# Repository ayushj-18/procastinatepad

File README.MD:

# procastinatepad
I like to procastinate alot so I made a hackpad to procastinate other stuff with it
## A hackpad with a 2x4 matrix rgb under every key. It uses solderable Cherry MX keyswitches. It also has a rotary encoder. For decorations, My mom will draw some DIY art here! that's why there's not much on onshape.

# Time spent: 41h

## CAD: Onshape

## Schematic: KiCAD

## PCB Layout: KiCAD

## 3D View: KiCAD

# BOM
-10x Cherry MX Switches
-10x 1N4148 Diodes
-10x SK6812 Mini LED 
-1x XIAO RP2040
-10x Blank DSA Keycaps
-4x M3x16 Bolt
-4x M3x4 Heatset
-1x EC11 ALPS Rotary Encoder
-1x PCB
-1kg filament from Amazon
-3D Printing from my friend's 3D printer (he lives 5 minutes away from me)

-Note: PCB is costing around $20 (with delivery) for both PCBWay and JLCPCB

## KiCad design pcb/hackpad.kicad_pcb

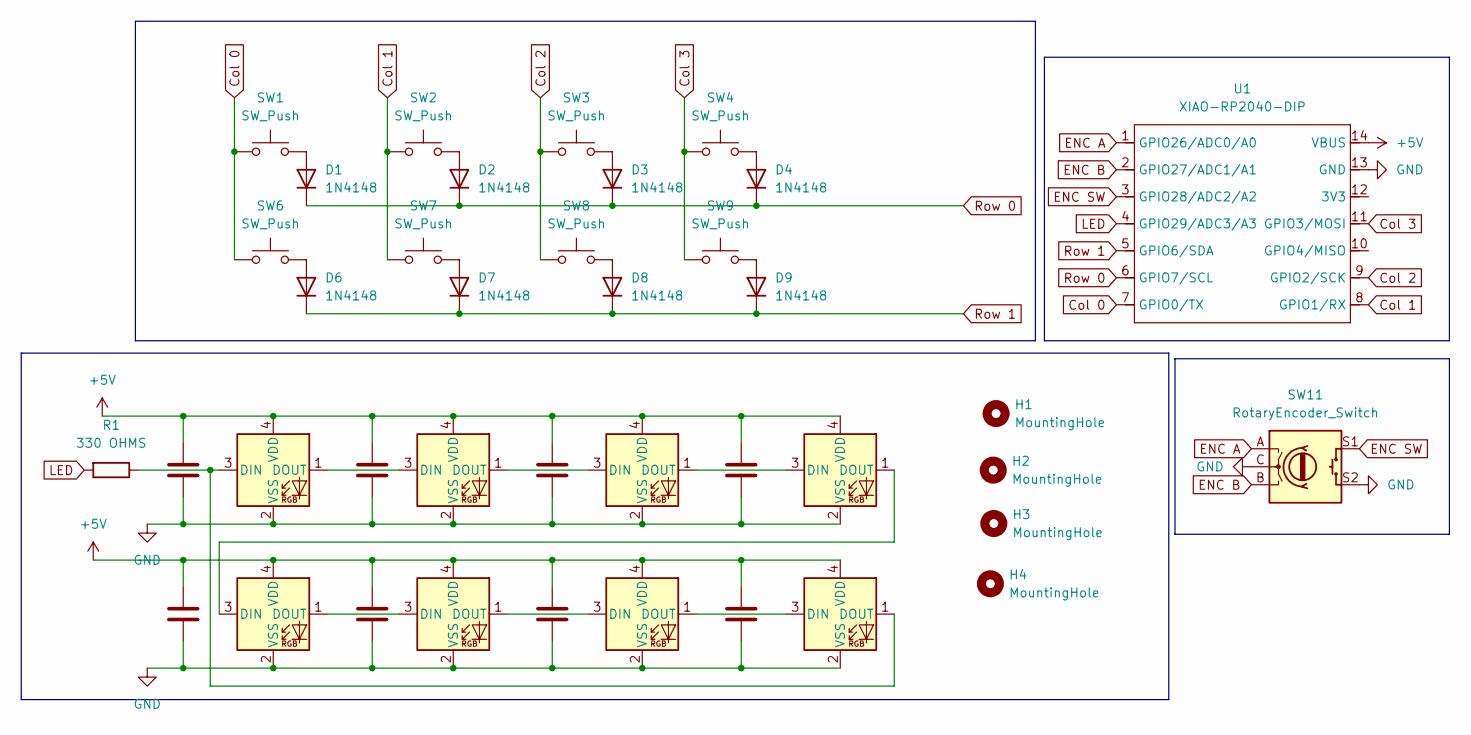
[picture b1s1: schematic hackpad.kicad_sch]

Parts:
C1, C2, C3, C4, C5, C7, C8, C9: C; C_0805_2012Metric
D1, D2, D3, D4, D6, D7, D8, D9: 1N4148; D_DO-35_SOD27_P7.62mm_Horizontal
D11, D12, D13, D14, D15, D16, D17, D19: SK6812MINI; LED_SK6812MINI_PLCC4_3.5x3.5mm_P1.75mm
H1, H2, H3, H4: MountingHole; MountingHole_2mm
R1: 330 OHMS; R_0805_2012Metric
SW1, SW2, SW3, SW4, SW6, SW7, SW8, SW9: SW_Push; Kailh-PG1353-Hotswap-1U
SW11: RotaryEncoder_Switch; RotaryEncoder_Alps_EC11E-Switch_Vertical_H20mm
U1: XIAO-RP2040-DIP

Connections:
+5V: C1.1, C2.1, C3.1, C4.1, C5.1, C7.1, C8.1, C9.1, D11.4 (VDD), D12.4 (VDD), D13.4 (VDD), D14.4 (VDD), D15.4 (VDD), D16.4 (VDD), D17.4 (VDD), D19.4 (VDD), U1.14 (VBUS); also elsewhere on the board
Col 0: SW1.1, SW6.1, U1.7 (GPIO0/TX)
Col 1: SW2.1, SW7.1, U1.8 (GPIO1/RX)
Col 2: SW3.1, SW8.1, U1.9 (GPIO2/SCK)
Col 3: SW4.1, SW9.1, U1.11 (GPIO3/MOSI)
ENC A: SW11.A, U1.1 (GPIO26/ADC0/A0)
ENC B: SW11.B, U1.2 (GPIO27/ADC1/A1)
ENC SW: SW11.S1, U1.3 (GPIO28/ADC2/A2)
GND: C1.2, C2.2, C3.2, C4.2, C5.2, C7.2, C8.2, C9.2, D11.2 (VSS), D12.2 (VSS), D13.2 (VSS), D14.2 (VSS), D15.2 (VSS), D16.2 (VSS), D17.2 (VSS), D19.2 (VSS), SW11.C, SW11.S2, U1.13 (GND); also elsewhere on the board
LED: R1.2, U1.4 (GPIO29/ADC3/A3)
unnamed: D1.2 (A), SW1.2
unnamed: D2.2 (A), SW2.2
unnamed: D3.2 (A), SW3.2
unnamed: D4.2 (A), SW4.2
unnamed: D6.2 (A), SW6.2
unnamed: D7.2 (A), SW7.2
unnamed: D8.2 (A), SW8.2
unnamed: D9.2 (A), SW9.2
unnamed: D11.3 (DIN), D17.1 (DOUT), R1.1
unnamed: D11.1 (DOUT), D12.3 (DIN)
unnamed: D12.1 (DOUT), D13.3 (DIN)
unnamed: D13.1 (DOUT), D19.3 (DIN)
unnamed: D14.3 (DIN), D19.1 (DOUT)
unnamed: D14.1 (DOUT), D15.3 (DIN)
unnamed: D15.1 (DOUT), D16.3 (DIN)
unnamed: D16.1 (DOUT), D17.3 (DIN)
Row 0: D1.1 (K), D2.1 (K), D3.1 (K), D4.1 (K), U1.6 (GPIO7/SCL)
Row 1: D6.1 (K), D7.1 (K), D8.1 (K), D9.1 (K), U1.5 (GPIO6/SDA)

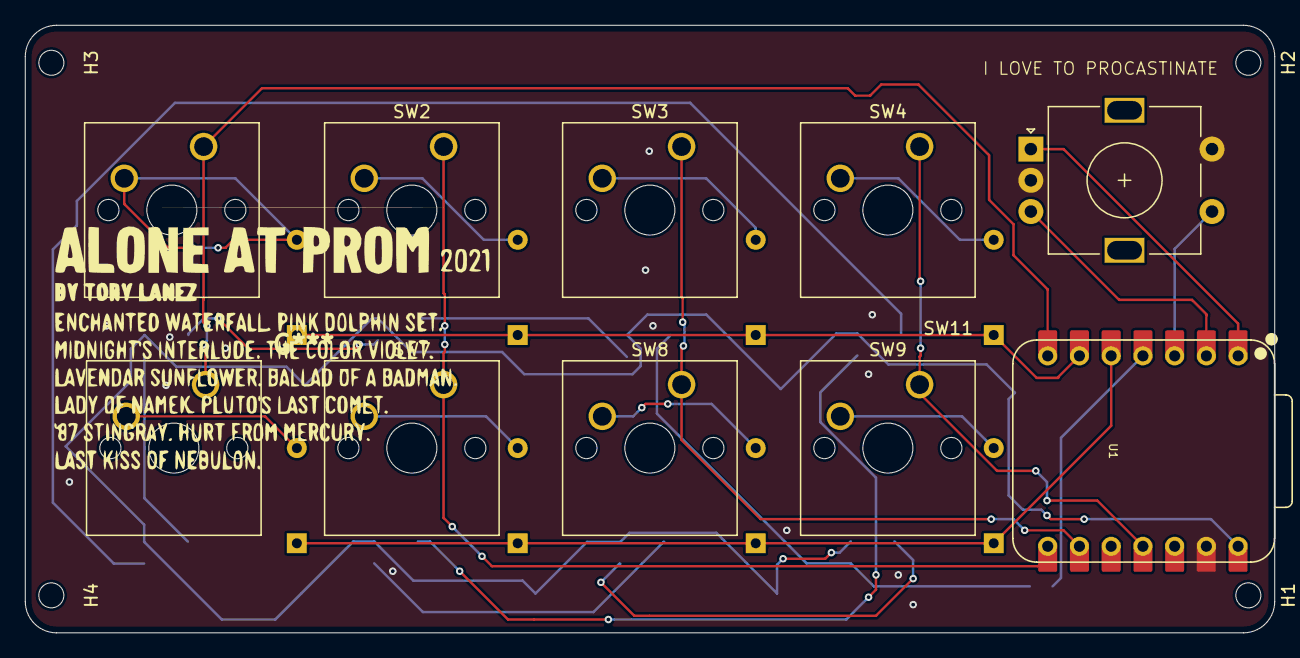
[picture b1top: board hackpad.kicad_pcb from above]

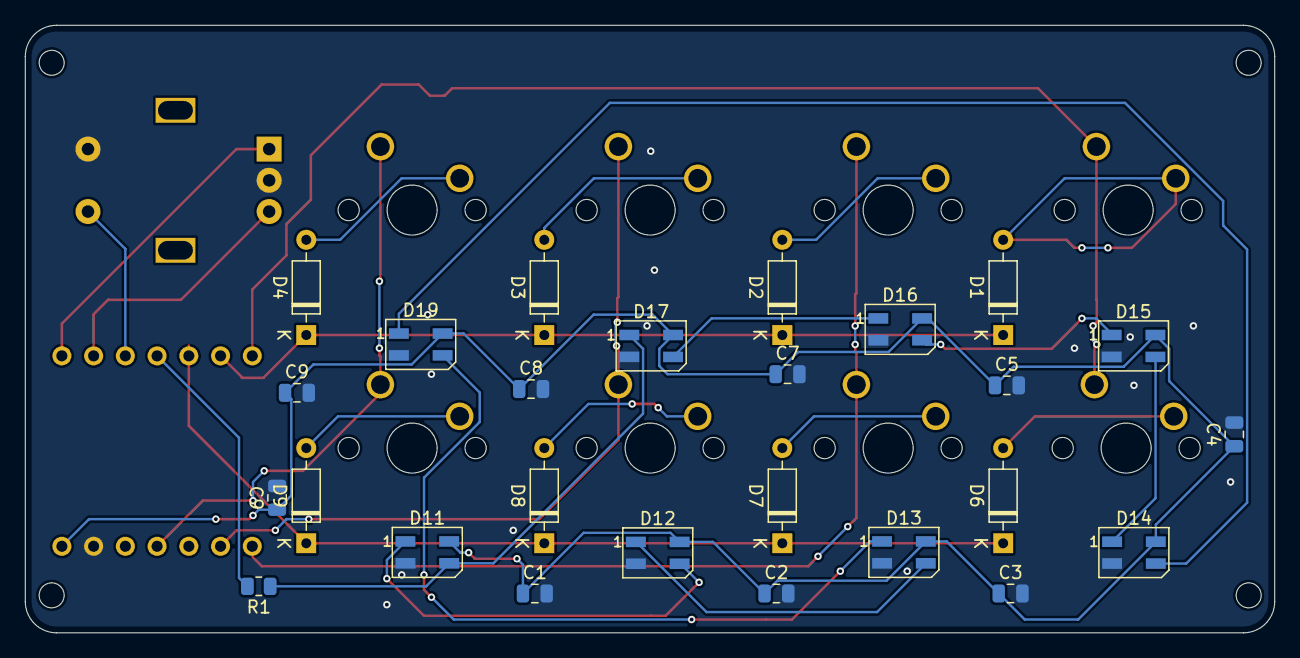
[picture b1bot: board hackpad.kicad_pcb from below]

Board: 2 copper layers, 100.0 x 48.6 mm, 40 parts (26 on the bottom side), 28 nets.

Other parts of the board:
C9#2: C; C_0805_2012Metric

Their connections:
+5V: C9#2.1; also elsewhere on the board
GND: C9#2.2; also elsewhere on the board

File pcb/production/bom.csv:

Designator,Footprint,Quantity,Value,LCSC Part #
"D1, D10, D2, D3, D4, D5, D6, D7, D8, D9",D_DO-35_SOD27_P7.62mm_Horizontal,10,1N4148,
"SW1, SW10, SW2, SW3, SW4, SW5, SW6, SW7, SW8, SW9",SW_Cherry_MX_1.00u_PCB,10,SW_Push,
SW11,RotaryEncoder_Alps_EC11E-Switch_Vertical_H20mm,1,RotaryEncoder_Switch,
U1,XIAO-RP2040-DIP,1,XIAO-RP2040-DIP,

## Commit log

2025-06-12 pcb stuff
2025-06-12 adwa
2025-06-12 cad folders
2025-06-13 firmware tweaks
2025-06-15 more cad files i forgot to add
2025-06-16 updated cad file
2025-06-17 updated cad file & grb solder files
2025-06-17 BOM added
2025-06-18 pcb files
2025-06-18 ok pls
2025-06-18 readme
2025-06-18 readme2
2025-06-18 updated code for rgb support
2025-06-18 added production
2025-06-18 Final 3d view changes, updated screenshots and updated CAD
2025-06-18 updated screenshots
2025-06-18 screenshots fixed
2025-06-18 updated screenshots pls work
2025-06-18 pcb production
2025-06-18 updated stl's because i decided to add mounting stuff
2025-06-18 Track and add STL file using Git LFS
2025-06-19 stl files
2025-06-19 Everything updated
2025-06-19 step files
2025-06-21 updated pcb final
